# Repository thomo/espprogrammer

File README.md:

# ESP Programmer

It is a small board which add just some logic to provide ESP-12 auto programming using a CP2104 board. Just connect the board to your ESP-12 board and you can upload your code like when using a Nodemcu board.

Design is based on information from

- <https://tttapa.github.io/ESP8266/Chap06%20-%20Uploading.html>
- <https://github.com/nodemcu/nodemcu-devkit-v1.0/blob/master/NODEMCU_DEVKIT_V1.0.PDF>

## Prototype

## Circuit

## PCB

The board can be ordered from OSH Park: <a href="https://oshpark.com/shared_projects/ITWmR2rG"></img></a>

## License

[MIT License](LICENSE)

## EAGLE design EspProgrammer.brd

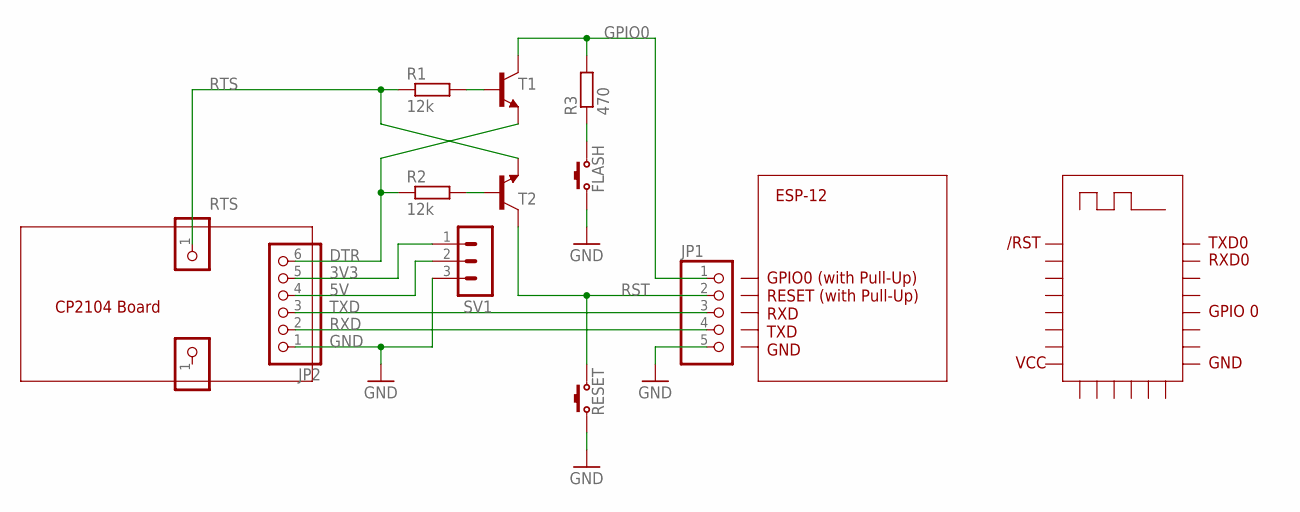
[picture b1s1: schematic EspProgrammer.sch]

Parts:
FLASH: KEY; SMD-BUTTON
JP1: PINHD-1X5/90; 1X05/90
JP2: PINHD-1X6; 1X06
LSP2, LSP3: PINHD-1X1; 1X01
R1, R2: 12k; R1206
R3: 470; R1206
RESET: KEY; SMD-BUTTON
SV1: MA03-1
T1, T2: BC817-40LT1SMD; SOT23-BEC

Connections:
3V3: JP2.5, SV1.1
5V: JP2.4, SV1.2
DTR: JP2.6, R2.1, T1.E
GND: FLASH.2, JP1.5, JP2.1, RESET.2, SV1.3
GPIO0: JP1.1, R3.2, T1.C
unnamed: R1.2, T1.B
unnamed: R2.2, T2.B
unnamed: FLASH.1, R3.1
RST: JP1.2, RESET.1, T2.C
RTS: LSP3.1, R1.1, T2.E
RXD: JP1.4, JP2.2
TXD: JP1.3, JP2.3

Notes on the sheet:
CP2104 Board
ESP-12
GPIO0 (with Pull-Up) RESET (with Pull-Up) RXD TXD GND
GPIO 0
/RST
VCC
GND
TXD0
RXD0

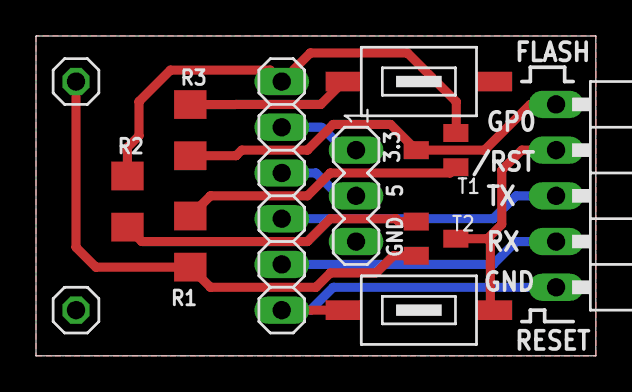
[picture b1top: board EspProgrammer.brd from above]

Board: 2 copper layers, 31.1 x 17.8 mm, 12 parts (0 on the bottom side), 12 nets.

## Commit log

2019-07-14 version 1.0
2019-07-14 add documentation
2020-12-09 change transistor package
2020-12-09 update link to project on OSH Park

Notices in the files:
parts and their libraries:
SparkFun-Aesthetics: Licensing: Creative Commons ShareAlike 4.0 International - https://creativecommons.org/licenses/by-sa/4.0
